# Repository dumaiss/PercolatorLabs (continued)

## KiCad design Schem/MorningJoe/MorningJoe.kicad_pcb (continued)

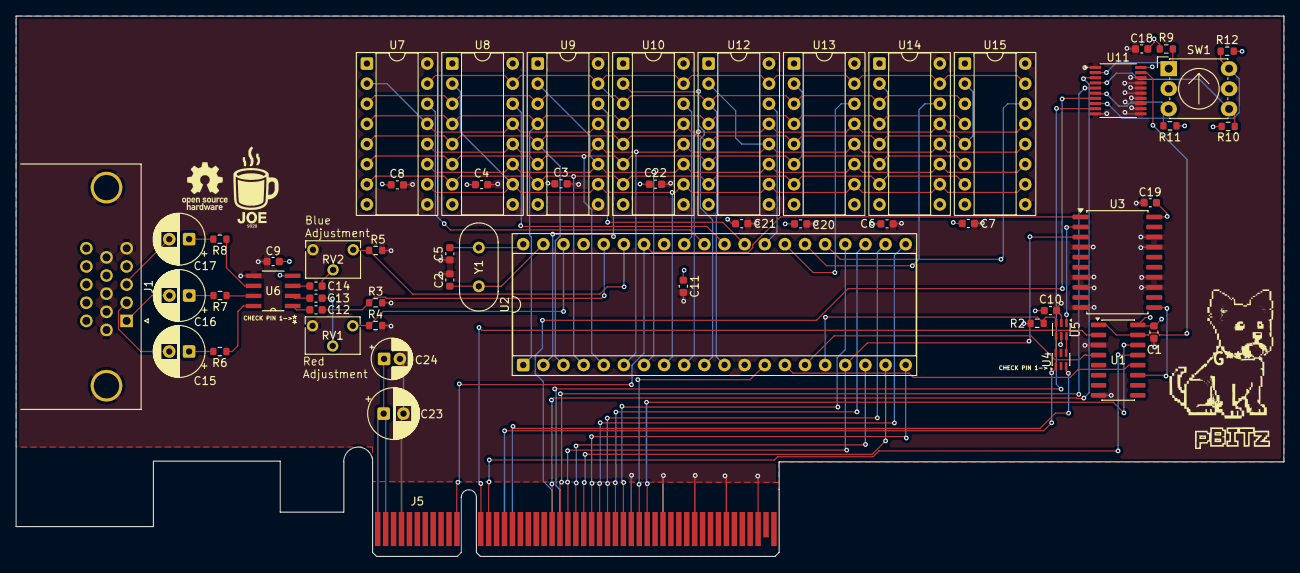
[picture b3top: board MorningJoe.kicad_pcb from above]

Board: 4 copper layers, 160.0 x 68.2 mm, 56 parts (0 on the bottom side), 71 nets.

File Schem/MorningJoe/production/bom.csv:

Designator,Footprint,Quantity,Value,LCSC Part #
"C1, C10, C11, C12, C13, C14, C18, C19, C20, C21, C22, C3, C4, C6, C7, C8, C9",0603,17,100n,
"C15, C16, C17, C23",CP_Radial_D6.3mm_P2.50mm,4,220u,
"C2, C5",0603,2,47p,
C24,CP_Radial_D5.0mm_P2.00mm,1,10u,
J1,DSUB-15-HD_Socket_Horizontal_P2.29x2.54mm_EdgePinOffset8.35mm_Housed_MountingHolesOffset10.89mm,1,DE15_Socket_HighDensity_MountingHoles,
"R10, R11, R12, R2, R9",0603,5,4K7,
"R3, R4, R5",0603,3,470,
"R6, R7, R8",0603,3,75,
"RV1, RV2",Potentiometer_Bourns_3266W_Vertical,2,R_Potentiometer,
SW1,Nidec_Copal_SH-7010C,1,SW_Coded_SH-7070,
U1,SOIC-16_3.9x9.9mm_P1.27mm,1,CD74HC139M96,
"U10, U12, U13, U14, U15, U7, U8, U9",DIP-16_W7.62mm_Socket,8,MK4164N,
U11,TSSOP-20_4.4x6.5mm_P0.65mm,1,74HC688,
U2,DIP-40_W15.24mm_Socket,1,TMS9928A,
U3,SOIC-20W_7.5x12.8mm_P1.27mm,1,SN74HC273DWR,
U4,SOT-363_SC-70-6,1,BAT54JW-7-F,
U5,SOT-363_SC-70-6,1,SN74LVC1G19DCKR,
U6,D8,1,THS7314DR,
Y1,Crystal_HC49-U_Vertical,1,MP107-E,

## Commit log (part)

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2026-06-08 Revise README with project details and structure
    Expanded README to include detailed project information, card specifications, and roadmap.
2026-06-08 Initial Commit for Percolated series
2026-06-08 Initial commit redux
2026-06-08 Squashed 'Code/VirtualDrip/backends/vrEmuTms9918/' content from commit dc40960
    git-subtree-dir: Code/VirtualDrip/backends/vrEmuTms9918
    git-subtree-split: dc40960954395e5f9cf47d1a2b0ce3da8482e390
2026-06-08 Still initial commit
2026-06-08 Still commiting stuff
2026-06-08 fixed vdrip and added libraries
2026-06-08 Added Morning Joe card
2026-06-14 Added the Lunch Crema video card
2026-06-15 Added both the Morning Joe and the Lunch Crema schematics, PCB, and KiCad library files.
2026-06-15 Review and Fixes
2026-06-15 Added bulk caps and fixed up the part numbers
2026-06-15 For some reason the OpenSource Hardware Logo had disapeared
2026-06-16 Cosmetic changes
2026-06-20 New Virtual Drip backend based on an emulator for a Yamaha V9958 video display processor along with the support in the Proxy.
    Proxy protocol has been extended and enhanced to support the new backend
    and its features, including new commands and capabilities specific to
    the V9958.
2026-06-20 Moved all datasheets to the pBITzPlatform Project
2026-06-21 V9958 based console completed!
2026-06-22 Fixed Sector errors
2026-06-24 support for 85x26 text grid in V9958 console
2026-06-28 New Afternoon Blend Sound Card Schematics
2026-06-28 Nasty fix for the Lunch Crema..... the pBITz interface bus connector was mirrored!
2026-06-28 Production Information
2026-06-28 Fixed an issue with the pBITz Interface connector where pinout was reversed. Generated the images, pdf and production files for the LunchCrema PCB.
2026-06-28 Just making sure the production files are up to date with the latest changes. Please review the modifications to the zip file, designators, and netlist before committing.
